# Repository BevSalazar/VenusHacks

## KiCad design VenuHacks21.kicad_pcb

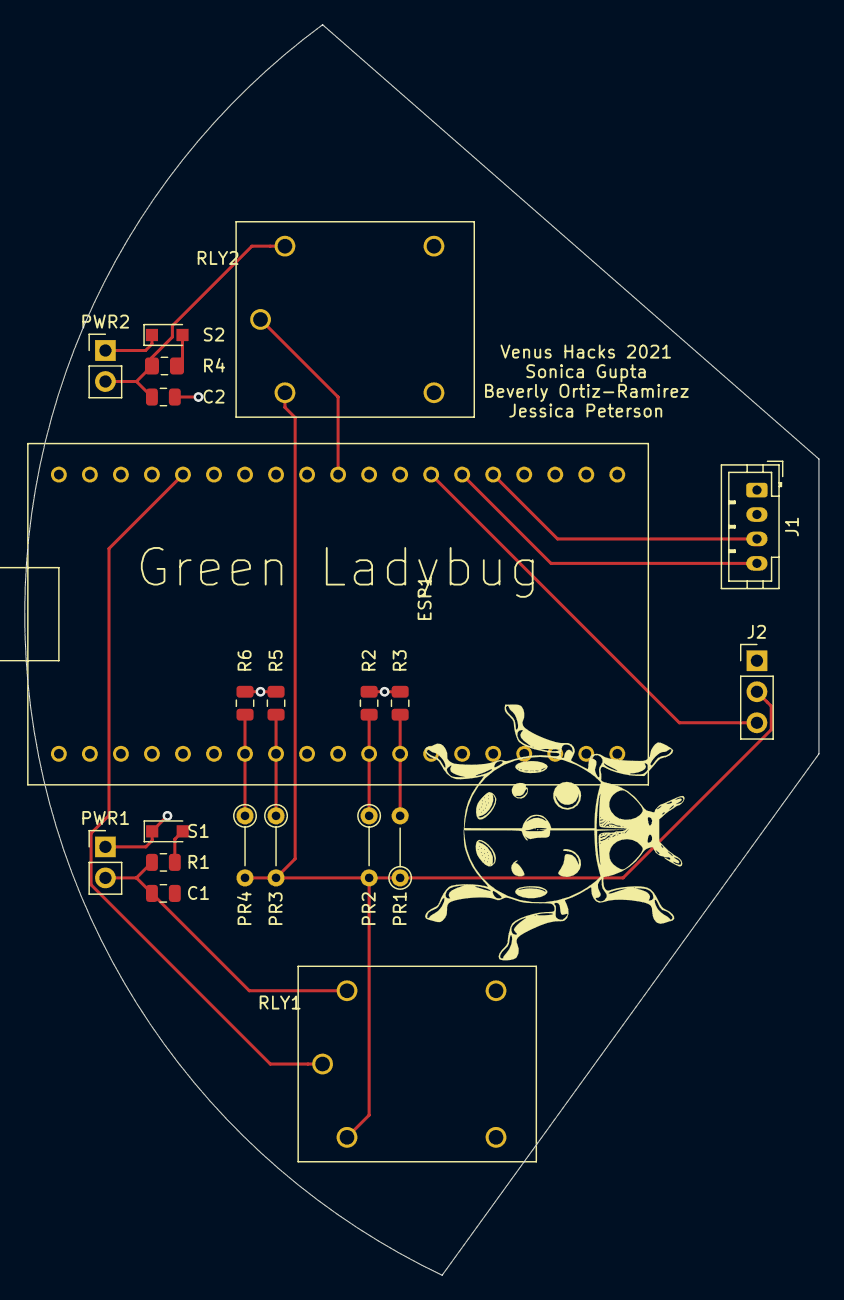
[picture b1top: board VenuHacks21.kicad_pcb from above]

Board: 2 copper layers, 65.0 x 102.4 mm, 21 parts (0 on the bottom side), 15 nets.

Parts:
C1, C2: 08055C104KAT2A; C_0805_2012Metric
ESP1: ESP32 -- DEVKIT; ESP32
J1: STEMMA soil; JST_PH_B4B-PH-K_1x04_P2.00mm_Vertical
J2: pH sensor; PinHeader_1x03_P2.54mm_Vertical
PR1, PR2, PR3, PR4: Photo resistor; R_Axial_DIN0204_L3.6mm_D1.6mm_P5.08mm_Vertical
PWR1, PWR2: 172286-1102; PinHeader_1x02_P2.54mm_Vertical
R1: R_0805_2012Metric
R2, R3, R5, R6: CRCW08051K00FKEA; R_0805_2012Metric
R4: R_0805_2012Metric_Pad1.15x1.40mm_HandSolder
RLY1, RLY2: G5LE-1A4 DC24; VHG5LE
S1, S2: Schottky; D_SOD-323_HandSoldering

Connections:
+3V3: J1.2, J2.2, PR1.1, PR2.2, PR3.2, PR4.2, RLY1.4, RLY2.4
/Battery: ESP1.15, RLY1.1
/Rechargable_Battery_Input: C1.2, PWR1.2, R1.2, RLY1.2
/Solar Panel: ESP1.10, RLY2.1
/Solar_Panel_Input: C2.2, PWR2.2, R4.2, RLY2.2
/V_Divider_1: ESP1.31, PR1.2, R3.2
/V_Divider_2: ESP1.30, PR2.1, R2.2
/V_Divider_3: ESP1.27, PR3.1, R5.2
/V_Divider_4: ESP1.26, PR4.1, R6.2
GND: C1.1, C2.1, ESP1.38, J1.1, J2.1, PWR1.1, PWR2.1, R2.1, R3.1, R5.1, R6.1, RLY1.3, RLY1.5, RLY2.3, RLY2.5, S1.1, S2.1
unnamed: ESP1.5, J1.3
unnamed: ESP1.6, J1.4
unnamed: ESP1.7, J2.3
unnamed: R1.1, S1.2
unnamed: R4.1, S2.2

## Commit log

2021-04-25 backend stuff
2021-04-25 mobile app stuff
2021-04-25 Add files via upload
    PCB files
2021-04-25 Lady bug model
    3D model
